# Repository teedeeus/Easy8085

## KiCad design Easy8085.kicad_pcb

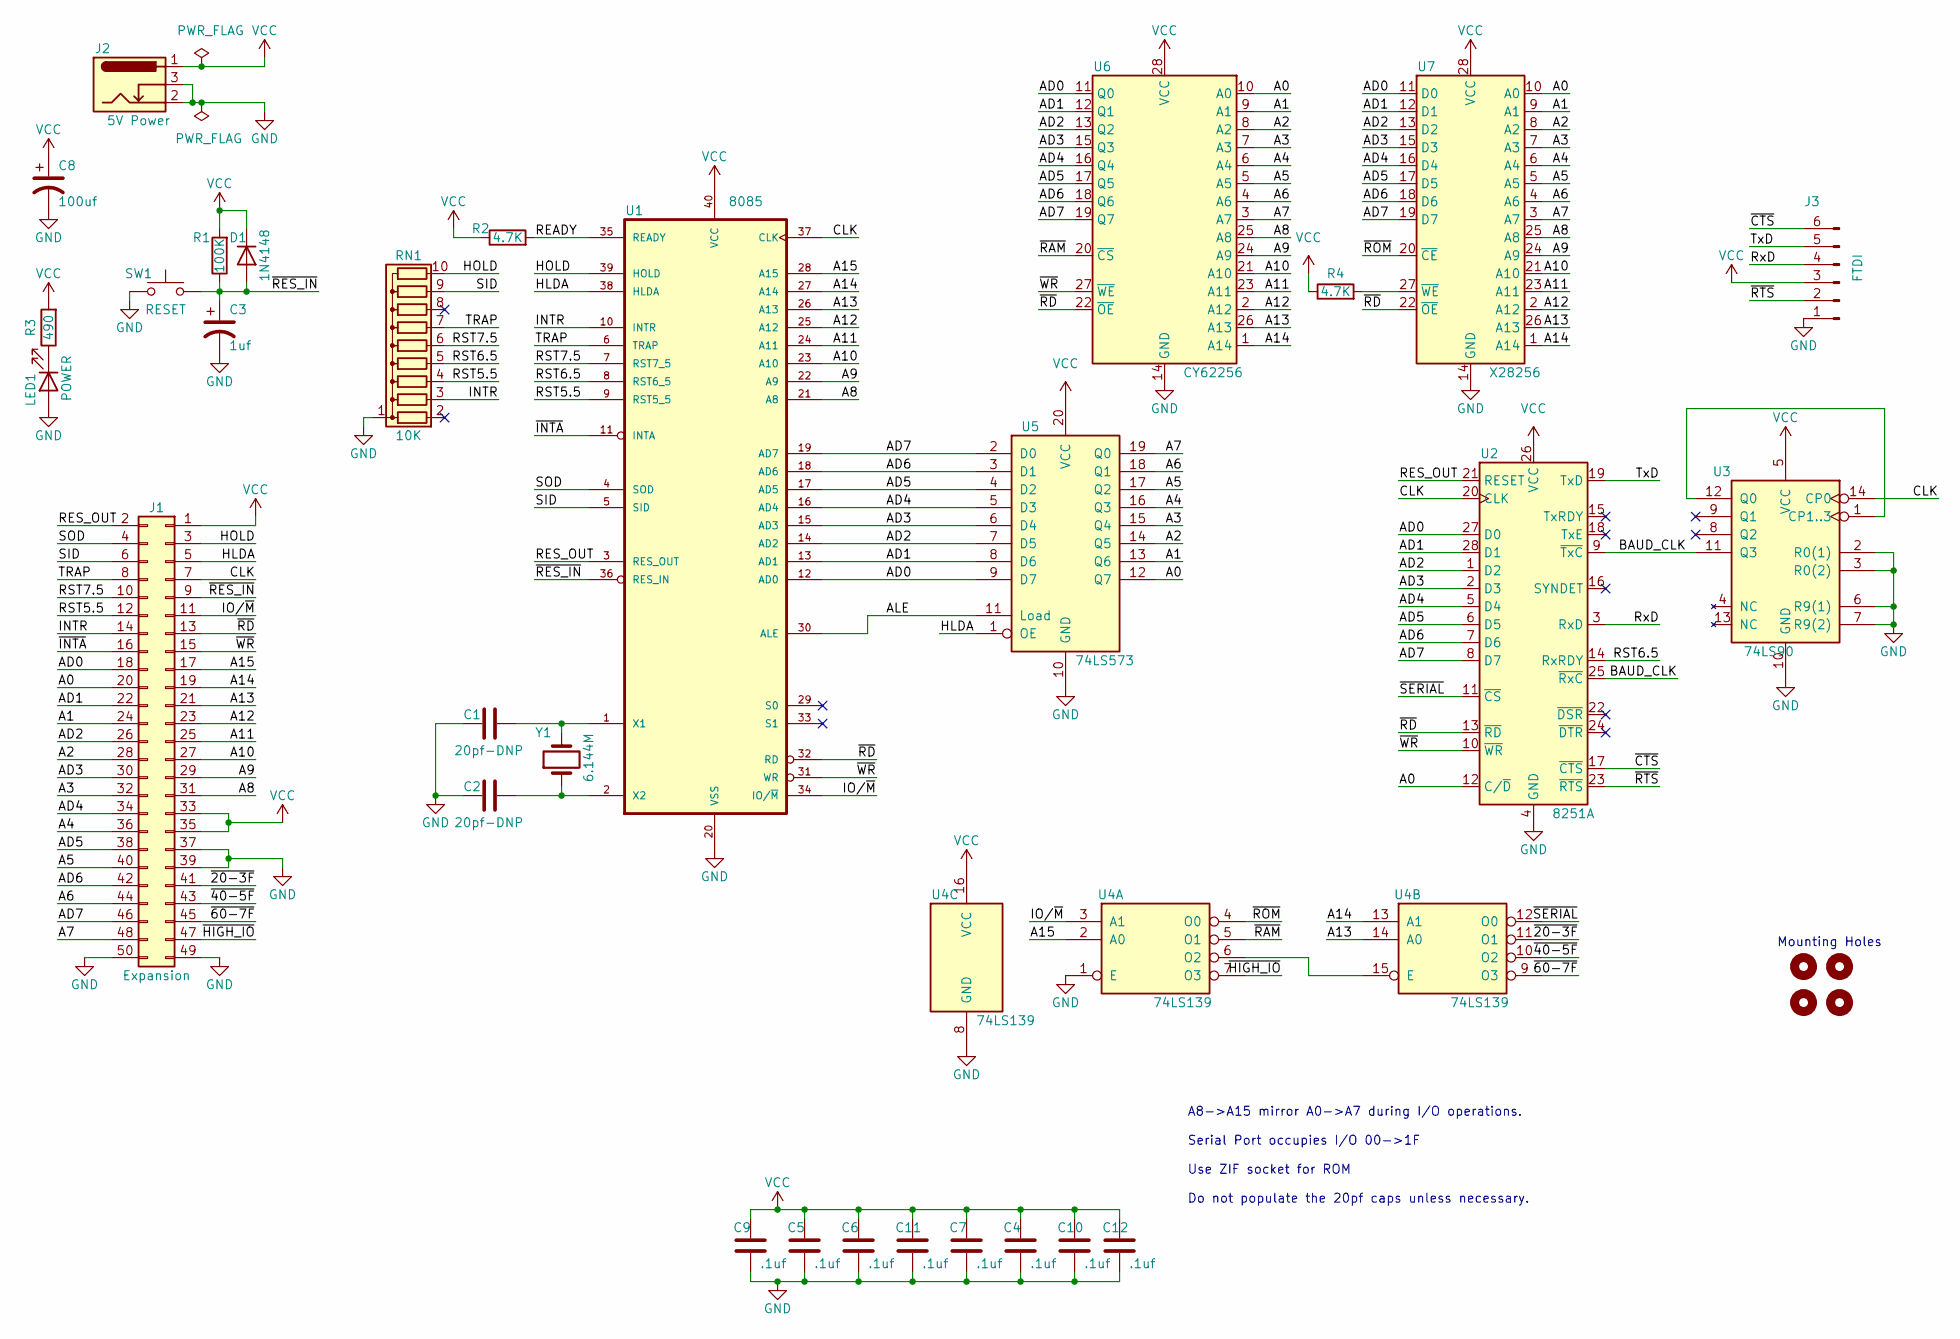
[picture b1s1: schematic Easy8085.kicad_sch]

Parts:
C1, C2: 20pf-DNP; C_Disc_D3.4mm_W2.1mm_P2.50mm
C3: 1uf; CP_Radial_D7.5mm_P2.50mm
C4, C5, C6, C7, C9, C10, C11, C12: .1uf; C_Disc_D3.4mm_W2.1mm_P2.50mm
C8: 100uf; CP_Radial_D7.5mm_P2.50mm
D1: 1N4148; D_DO-35_SOD27_P7.62mm_Horizontal
H1, H2, H3, H4: MountingHole; MountingHole_2.7mm_M2.5
J1: Expansion; PinHeader_2x25_P2.54mm_Vertical
J2: 5V Power; BarrelJack_GCT_DCJ200-10-A_Horizontal
J3: FTDI; PinSocket_1x06_P2.54mm_Horizontal
LED1: POWER; LED_D5.0mm
R1: 100K; R_Axial_DIN0204_L3.6mm_D1.6mm_P7.62mm_Horizontal
R2, R4: 4.7K; R_Axial_DIN0204_L3.6mm_D1.6mm_P7.62mm_Horizontal
R3: 490; R_Axial_DIN0204_L3.6mm_D1.6mm_P7.62mm_Horizontal
RN1: 10K; R_Array_SIP10
SW1: RESET; SW_PUSH_6mm_H5mm
U1: 8085; DIP-40_W15.24mm_Socket
U2: 8251A; DIP-28_W15.24mm_Socket
U3: 74LS90; DIP-14_W7.62mm_Socket
U4: 74LS139; DIP-16_W7.62mm_Socket
U5: 74LS573; DIP-20_W7.62mm_Socket
U6: CY62256; DIP-28_W15.24mm_Socket
U7: X28256; DIP_Socket-28_W11.9_W12.7_W15.24_W17.78_W18.5_3M_228-1277-0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
Y1: 6.144M; Crystal_HC49-4H_Vertical

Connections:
/A0: J1.20, U2.12 (C/~D), U5.12 (Q7), U6.10 (A0), U7.10 (A0)
/A1: J1.24, U5.13 (Q6), U6.9 (A1), U7.9 (A1)
/A2: J1.28, U5.14 (Q5), U6.8 (A2), U7.8 (A2)
/A3: J1.32, U5.15 (Q4), U6.7 (A3), U7.7 (A3)
/A4: J1.36, U5.16 (Q3), U6.6 (A4), U7.6 (A4)
/A5: J1.40, U5.17 (Q2), U6.5 (A5), U7.5 (A5)
/A6: J1.44, U5.18 (Q1), U6.4 (A6), U7.4 (A6)
/A7: J1.48, U5.19 (Q0), U6.3 (A7), U7.3 (A7)
/A8: J1.31, U1.21 (A8), U6.25 (A8), U7.25 (A8)
/A9: J1.29, U1.22 (A9), U6.24 (A9), U7.24 (A9)
/A10: J1.27, U1.23 (A10), U6.21 (A10), U7.21 (A10)
/A11: J1.25, U1.24 (A11), U6.23 (A11), U7.23 (A11)
/A12: J1.23, U1.25 (A12), U6.2 (A12), U7.2 (A12)
/A13: J1.21, U1.26 (A13), U4.14 (A0), U6.26 (A13), U7.26 (A13)
/A14: J1.19, U1.27 (A14), U4.13 (A1), U6.1 (A14), U7.1 (A14)
/A15: J1.17, U1.28 (A15), U4.2 (A0)
/AD0: J1.18, U1.12 (AD0), U2.27 (D0), U5.9 (D7), U6.11 (Q0), U7.11 (D0)
/AD1: J1.22, U1.13 (AD1), U2.28 (D1), U5.8 (D6), U6.12 (Q1), U7.12 (D1)
/AD2: J1.26, U1.14 (AD2), U2.1 (D2), U5.7 (D5), U6.13 (Q2), U7.13 (D2)
/AD3: J1.30, U1.15 (AD3), U2.2 (D3), U5.6 (D4), U6.15 (Q3), U7.15 (D3)
/AD4: J1.34, U1.16 (AD4), U2.5 (D4), U5.5 (D3), U6.16 (Q4), U7.16 (D4)
/AD5: J1.38, U1.17 (AD5), U2.6 (D5), U5.4 (D2), U6.17 (Q5), U7.17 (D5)
/AD6: J1.42, U1.18 (AD6), U2.7 (D6), U5.3 (D1), U6.18 (Q6), U7.18 (D6)
/AD7: J1.46, U1.19 (AD7), U2.8 (D7), U5.2 (D0), U6.19 (Q7), U7.19 (D7)
/ALE: U1.30 (ALE), U5.11 (Load)
/BAUD_CLK: U2.9 (~TxC), U2.25 (~RxC), U3.11 (Q3)
/CLK: J1.7, U1.37 (CLK), U2.20 (CLK), U3.14 (CP0)
/HLDA: J1.5, U1.38 (HLDA), U5.1 (OE)
/HOLD: J1.3, RN1.10 (R9), U1.39 (HOLD)
/INTR: J1.14, RN1.3 (R2), U1.10 (INTR)
/IO/~M: J1.11, U1.34 (IO/~M), U4.3 (A1)
/READY: R2.2, U1.35 (READY)
/RES_OUT: J1.2, U1.3 (RES_OUT), U2.21 (RESET)
/RST5.5: J1.12, RN1.4 (R3), U1.9 (RST5_5)
/RST6.5: RN1.5 (R4), U1.8 (RST6_5), U2.14 (RxRDY)
/RST7.5: J1.10, RN1.6 (R5), U1.7 (RST7_5)
/RxD: J3.4, U2.3 (RxD)
/SID: J1.6, RN1.9 (R8), U1.5 (SID)
/SOD: J1.4, U1.4 (SOD)
/TRAP: J1.8, RN1.7 (R6), U1.6 (TRAP)
/TxD: J3.5, U2.19 (TxD)
/~20-3F: J1.41, U4.11 (O1)
/~40-5F: J1.43, U4.10 (O2)
/~60-7F: J1.45, U4.9 (O3)
/~CTS: J3.6, U2.17 (~CTS)
/~HIGH_IO: J1.47, U4.7 (O3)
/~INTA: J1.16, U1.11 (INTA)
/~RAM: U4.5 (O1), U6.20 (~CS)
/~RD: J1.13, U1.32 (RD), U2.13 (~RD), U6.22 (~OE), U7.22 (~OE)
/~RES_IN: C3.1, D1.2 (A), J1.9, R1.1, SW1.2, U1.36 (RES_IN)
/~ROM: U4.4 (O0), U7.20 (~CE)
/~RTS: J3.2, U2.23 (~RTS)
/~SERIAL: U2.11 (~CS), U4.12 (O0)
/~WR: J1.15, U1.31 (WR), U2.10 (~WR), U6.27 (~WE)
GND: C1.2, C2.2, C3.2, C4.2, C5.2, C6.2, C7.2, C8.2, C9.2, C10.2, C11.2, C12.2, J1.37, J1.39, J1.49, J1.50, J2.2, J2.3, J3.1, LED1.2 (A), RN1.1 (common), SW1.1, U1.20 (VSS), U2.4 (GND), U3.2 (R0(1)), U3.3 (R0(2)), U3.6 (R9(1)), U3.7 (R9(2)), U3.10 (GND), U4.1 (E), U4.8 (GND), U5.10 (GND), U6.14 (GND), U7.14 (GND)
unnamed: C1.1, U1.1 (X1), Y1.2
unnamed: C2.1, U1.2 (X2), Y1.1
unnamed: LED1.1 (K), R3.1
unnamed: R4.2, U7.27 (~WE)
unnamed: U3.1 (CP1..3), U3.12 (Q0)
unnamed: U4.6 (O2), U4.15 (E)
VCC: C4.1, C5.1, C6.1, C7.1, C8.1, C9.1, C10.1, C11.1, C12.1, D1.1 (K), J1.1, J1.33, J1.35, J2.1, J3.3, R1.2, R2.1, R3.2, R4.1, U1.40 (VCC), U2.26 (VCC), U3.5 (VCC), U4.16 (VCC), U5.20 (VCC), U6.28 (VCC), U7.28 (VCC)

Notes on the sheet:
A8->A15 mirror A0->A7 during I/O operations. Serial Port occupies I/O 00->1F Use ZIF socket for ROM Do not populate the 20pf caps unless necessary.
Mounting Holes

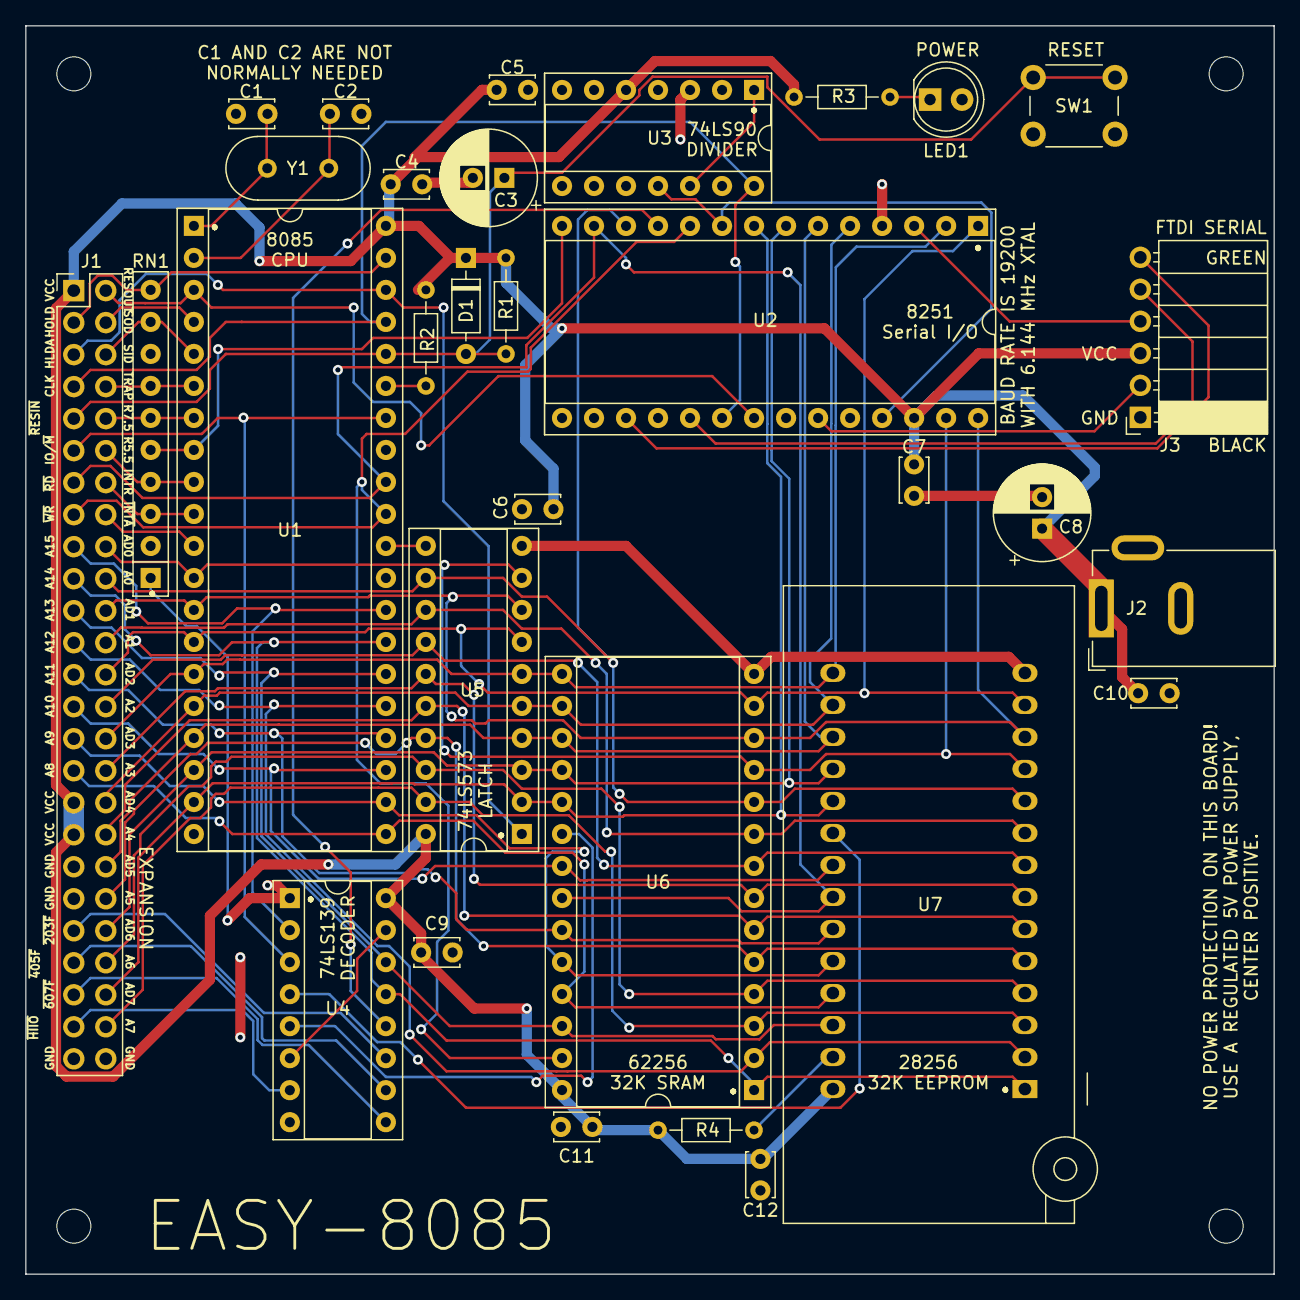
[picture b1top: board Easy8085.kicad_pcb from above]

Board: 2 copper layers, 99.1 x 99.1 mm, 35 parts (0 on the bottom side), 62 nets.

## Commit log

2022-02-08 re-working PCB and schematic to seperate expansion connector and reduce parts.
2022-02-08 Continuing PCB layout.
2022-02-08 Still working on layout - what a pain.
2022-02-08 Changing to 4 layer board.
2022-02-09 4 layer board continued...
2022-02-10 Finally making progress on the layout.
2022-02-10 Finish routing the board
2022-02-10 Added kicad .gitignore.
2022-02-10 Delete Easy8085-backups directory
    added this folder to .gitignore.
2022-02-10 Finished board routing. Need to fix silkscreen
2022-02-11 Fixed errors in PCB layout
2022-02-11 Fixed mounting holes and re-annotated schematic
2022-02-11 Finished layout
2022-02-13 Finished layout, produced gerbers for JLC-PCB
2022-02-14 Found and fixed error with AD0-7 reversed on UART
